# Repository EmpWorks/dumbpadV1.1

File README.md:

# dumbpadV1.1
dumbpad with oled support

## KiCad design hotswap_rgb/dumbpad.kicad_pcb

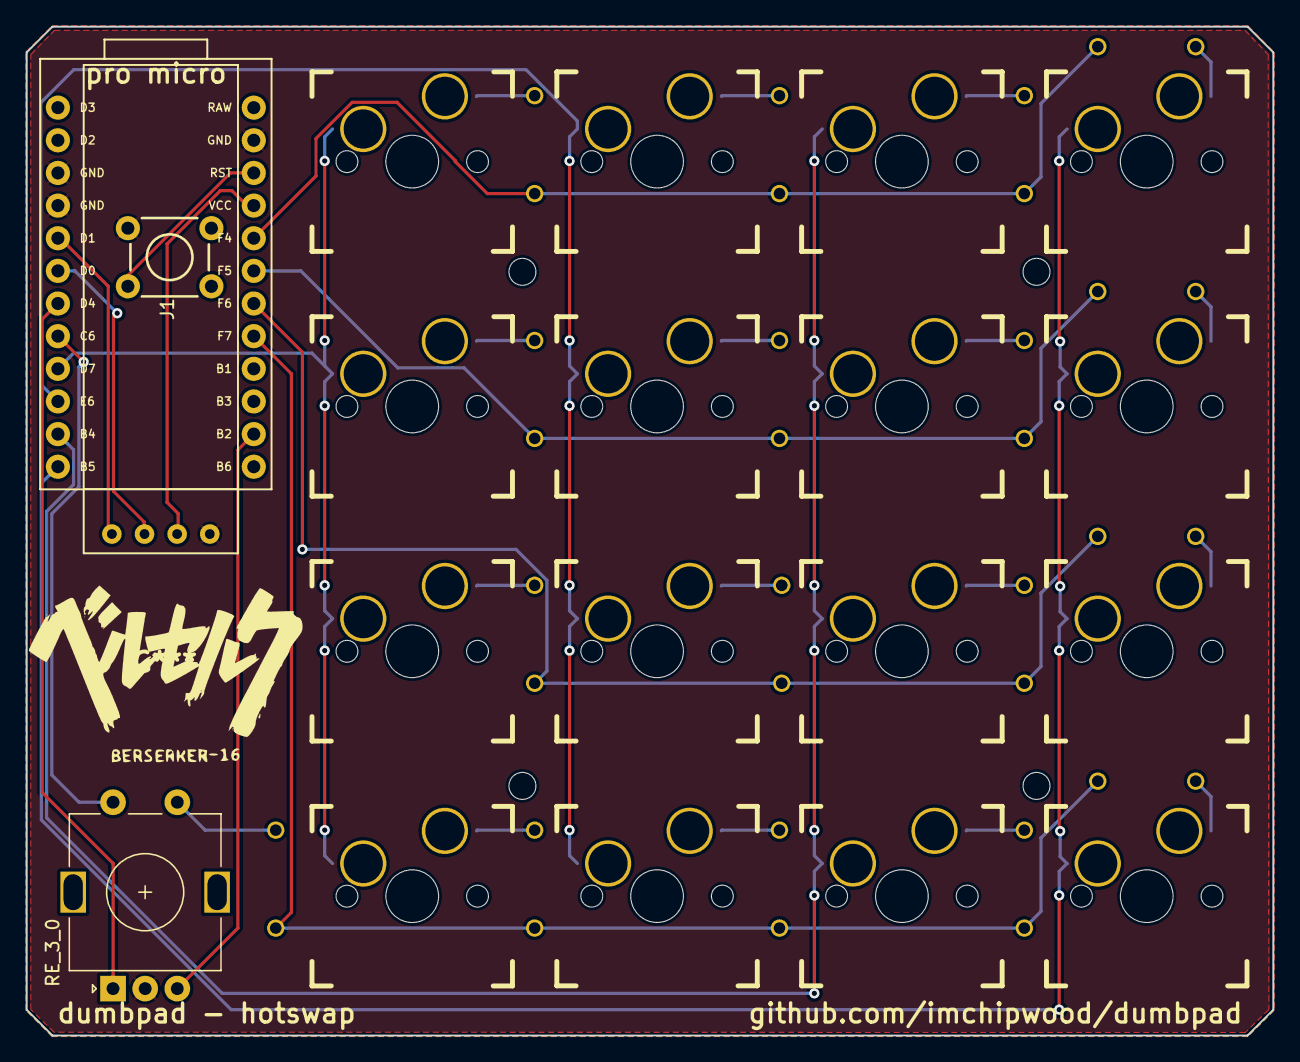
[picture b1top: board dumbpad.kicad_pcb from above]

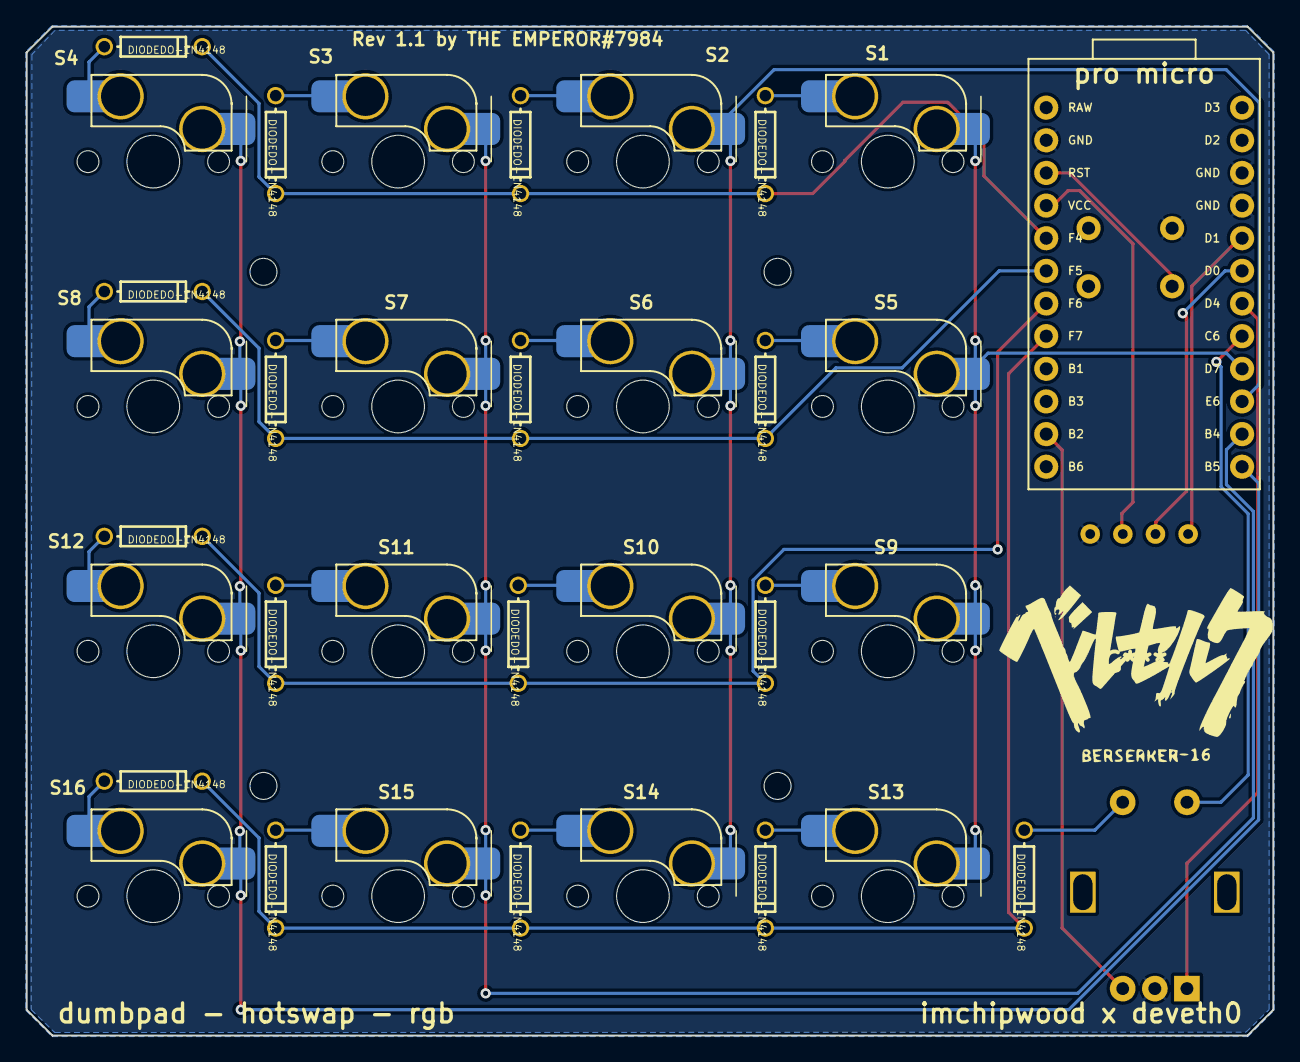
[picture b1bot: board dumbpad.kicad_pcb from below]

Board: 2 copper layers, 97.0 x 78.5 mm, 37 parts (33 on the bottom side), 33 nets.

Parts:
B1: SPARKFUN_PRO_MICRO
D1, D2, D3, D4, D5, D6, D7, D8, D9, D10, D11, D12, D13, D14, D15, D16, D20: DIODEDO-1N4148; DO-1N4148
J1: Conn_01x04_Male; ssd1306 128x32 oled
RE_3_0: CHERRY-MX-ENCODER; RotaryEncoder_Alps_EC11E-Switch_Vertical_H20mm
S1, S2, S3, S4, S5, S6, S7, S8, S9, S10, S11, S12, S13, S14, S15, S16: MOMENTARY-SWITCH-SPST-LED-PTH-CHERRY; Kailh-CPG151101S11_MX_Socket-1.00u
S17: MOMENTARY-SWITCH-SPST-PTH-6.0MM; TACTILE_SWITCH_PTH_6.0MM

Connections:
/COL0: B1.8 (*5), RE_3_0.S2 (2)
/COL1: B1.9 (*6), S1.S2 (2), S5.S2 (2), S9.S2 (2), S13.S2 (2)
/COL2: B1.10 (7), S2.S2 (2), S6.S2 (2), S10.S2 (2), S14.S2 (2)
/COL3: B1.11 (8), S3.S2 (2), S7.S2 (2), S11.S2 (2), S15.S2 (2)
/COL4: B1.12 (*9), S4.S2 (2), S8.S2 (2), S12.S2 (2), S16.S2 (2)
/ENCODER0_L0: B1.14 (11(MOSI)), RE_3_0.B
/ENCODER0_L1: B1.7 (4), RE_3_0.A
/RESET: B1.22 (RESET), S17.3 (2)
/ROW0: B1.20 (A3), D1.C, D2.C, D3.C, D4.C
/ROW1: B1.19 (A2), D5.C, D6.C, D7.C, D8.C
/ROW2: B1.18 (A1), D9.C, D10.C, D11.C, D12.C
/ROW3: B1.17 (A0), D13.C, D14.C, D15.C, D16.C, D20.C
GND: B1.3 (GND@1), B1.4 (GND), B1.23 (GND@2), J1.1, RE_3_0.C, S17.1
unnamed: D1.A, S1.S1 (1)
unnamed: D2.A, S2.S1 (1)
unnamed: D3.A, S3.S1 (1)
unnamed: D4.A, S4.S1 (1)
unnamed: D5.A, S5.S1 (1)
unnamed: D6.A, S6.S1 (1)
unnamed: D7.A, S7.S1 (1)
unnamed: D8.A, S8.S1 (1)
unnamed: D9.A, S9.S1 (1)
unnamed: D10.A, S10.S1 (1)
unnamed: D11.A, S11.S1 (1)
unnamed: D12.A, S12.S1 (1)
unnamed: D13.A, S13.S1 (1)
unnamed: D14.A, S14.S1 (1)
unnamed: D15.A, S15.S1 (1)
unnamed: D16.A, S16.S1 (1)
unnamed: D20.A, RE_3_0.S1 (1)
VCC: B1.21 (VCC), J1.2
scl: B1.6 (*3), J1.3
sda: B1.5 (2), J1.4
